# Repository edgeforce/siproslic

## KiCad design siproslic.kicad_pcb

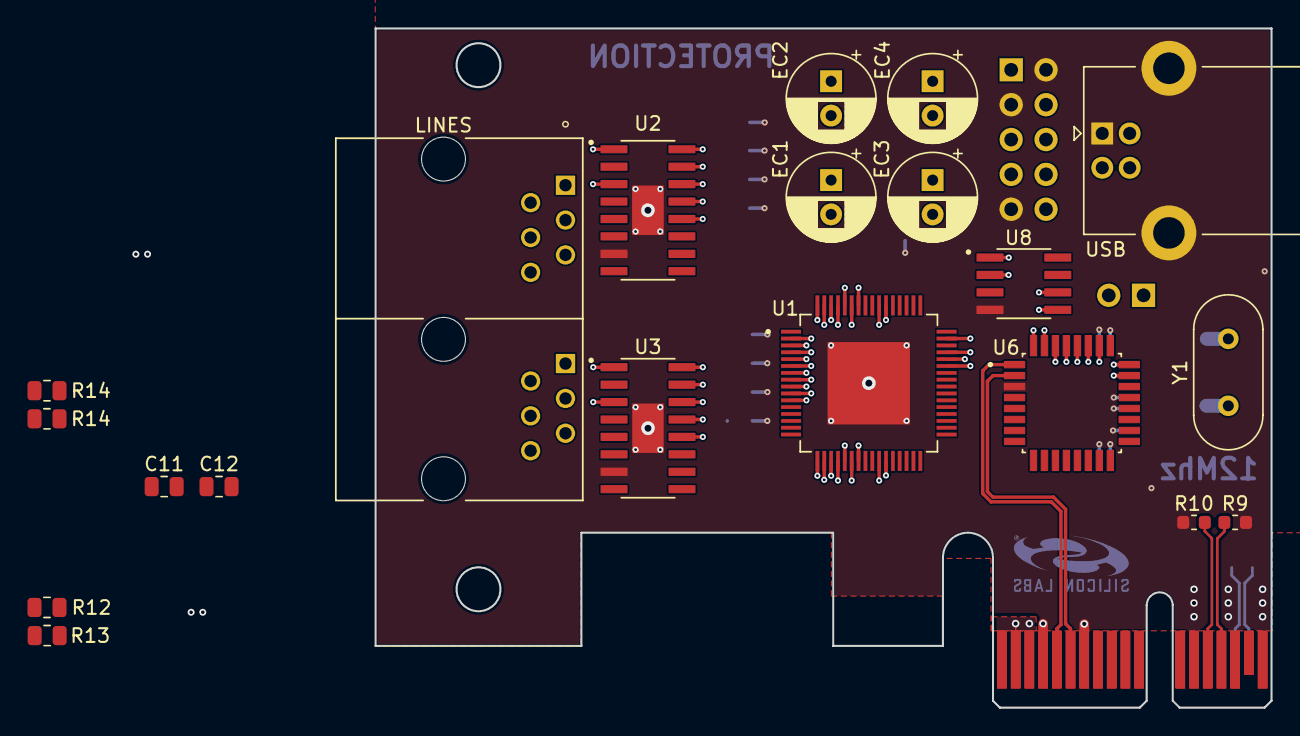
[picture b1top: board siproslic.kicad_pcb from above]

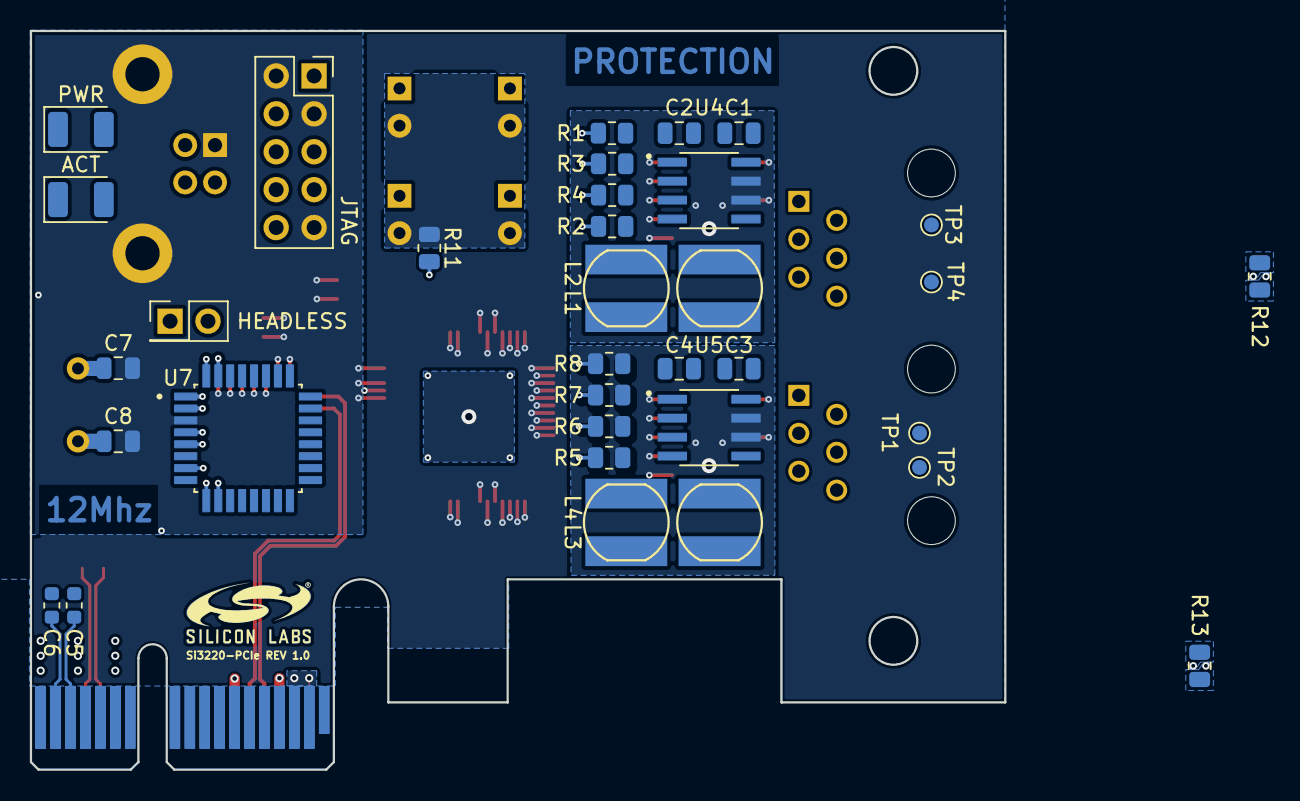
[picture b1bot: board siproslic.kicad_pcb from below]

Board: 4 copper layers, 65.3 x 49.5 mm, 58 parts (34 on the bottom side), 76 nets.

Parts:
ACT: CP_EIA-3528-21_Kemet-B
C1, C2, C3, C4, C7, C8: C_0805_2012Metric
C5, C6: 100n; C_0603_1608Metric
C11, C12: R_0805_2012Metric
EC1, EC2, EC3, EC4: CP_Radial_D6.3mm_P2.50mm
HEADLESS: PinHeader_2x01_P2.54mm_Vertical
J1: PCIexpress_bracket; PCIexpress_bracket_low
J2, J2#2: PCIexpress_x1
JTAG: PinHeader_2x05_P2.54mm_Vertical
L1, L2, L3, L4: CD54
LINES: ASSMANN_A-2004-1-4-LP-N-R
LOGO: LOGO; SILABS
PWR: CP_EIA-3528-21_Kemet-B
R1, R2, R3, R4, R5, R6, R7, R8, R11, R12, R12#2, R13, R13#2, R14, R14#2: R_0805_2012Metric
R9, R10: 49.9; R_0603_1608Metric
TP1, TP2, TP3, TP4: TestPoint_Pad_D1.0mm
U1: QFP50P1200X1200X120-64N
U2, U3: SOIC127P600X175-16N
U4, U5, U8: SOIC127P599X175-8N
U6: C8051F389-B-GQ; QFP80P900X900X160-32N
U7: C8051F320-GQ; QFP80P900X900X160-32N
USB: USB_B_Lumberg_2411_02_Horizontal
Y1: Crystal_HC49-U_Vertical

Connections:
+3.3VA: J2.B10, J2#2.B10
+3V3: J2.A9, J2.A10, J2.B8, J2#2.A9, J2#2.A10, J2#2.B8, JTAG.1, U6.6, U7.6, U8.8
+5V: JTAG.10, U7.7, USB.4
+12V: J2.A2, J2.A3, J2.B1, J2.B2, J2.B3, J2#2.A2, J2#2.A3, J2#2.B1, J2#2.B2, J2#2.B3
/PCIexpress_connector/_PER0_N: C6.1, J2.A17, J2#2.A17
/PCIexpress_connector/_PER0_P: C5.2, J2.A16, J2#2.A16
/PET0_N: J2.B15, J2#2.B15, R9.1
/PET0_P: J2.B14, J2#2.B14, R10.1
/REFCLK+: J2.A13, J2#2.A13
/REFCLK-: J2.A14, J2#2.A14
/SMCLK: J2.B5, J2#2.B5, U6.1
/SMDAT: J2.B6, J2#2.B6, U6.2
/TCK: J2.A5, J2#2.A5
/TDI: J2.A6, J2#2.A6
/TDO: J2.A7, J2#2.A7
/TMS: J2.A8, J2#2.A8
/~PERST: J2.A11, J2#2.A11
/~PRSNT1: J2.A1, J2#2.A1
/~PRSNT2x1: J2.B17, J2#2.B17
/~TRST: J2.B9, J2#2.B9
/~WAKE: J2.B11, J2#2.B11
C2CK: JTAG.7, U7.9
C2D: JTAG.4, U7.10
CAPMa: EC1.1, U1.7
CAPMb: EC3.1, U1.10
CAPPa: EC2.1, U1.6
CAPPb: EC4.1, U1.11
CSB: U1.47, U6.26
CSF: U6.27, U8.1
D+: U7.4, USB.3
D-: U7.5, USB.2
GND: C7.2, C8.2, J2.A4, J2.A12, J2.A15, J2.A18, J2.B4, J2.B7, J2.B13, J2.B16, J2.B18, J2#2.A4, J2#2.A12, J2#2.A15, J2#2.A18, J2#2.B4, J2#2.B7, J2#2.B13, J2#2.B16, J2#2.B18, JTAG.2, JTAG.3, JTAG.9, R9.2, R10.2, U1.65, U2.7, U2.17, U3.7, U3.17, U4.6, U4.7, U5.6, U5.7, U6.3, U7.3, U8.4, USB.1, USB.5
IREF: R11.1, U1.9
IRINGNa: U1.59, U2.12
IRINGNb: U1.22, U3.12
IRINGPa: U1.55, U2.13
IRINGPb: U1.26, U3.13
ITIPNa: U1.60, U2.15
ITIPNb: U1.21, U3.15
ITIPPa: U1.58, U2.16
ITIPPb: U1.23, U3.16
MISO: U1.44, U6.30, U8.2
MOSI: U1.45, U6.29, U8.5
N011: C1.1, R1.1, U2.1, U4.1
N012: C2.1, R2.1, U2.3, U4.4
N021: C4.1, R5.1, U3.1, U5.1
N022: C3.1, R6.1, U3.3, U5.4
N0101: C1.2, R3.1
N0102: C2.2, R4.1
N0201: C4.2, R7.1
N0202: C3.2, R8.1
unnamed: J2.B12, J2#2.B12
QGND: EC1.2, EC2.2, EC3.2, EC4.2, R11.2, U1.8
RING1: L2.P$1, TP2.1
RING2: L4.P$1, LINES.4, TP4.1
RNIa: R13#2.1, U1.4
RNOa: R13#2.2, U1.5
RPIa: R12#2.2, U1.3
RPOa: R12#2.1, U1.2
SCLK: U1.43, U6.28, U8.6
SRINGACa: R4.2, U1.62
SRINGACb: R8.2, U1.19
SRINGDCa: R2.2, U1.61
SRINGDCb: R6.2, U1.20
STIPACa: R3.2, U1.63
STIPACb: R7.2, U1.18
STIPDCa: R1.2, U1.64
STIPDCb: R5.2, U1.17
THERMa: U1.54, U2.14
THERMb: U1.27, U3.14
TIP1: L1.P$1, LINES.3, TP1.1
TIP2: L3.P$1, TP3.1
XCLK: U6.24, U7.1
XDAT: U6.23, U7.2
XTAL1: C8.1, U6.32, U7.32, Y1.1
XTAL2: C7.1, U6.31, U7.31, Y1.2

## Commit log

2024-04-23 First initial commit
